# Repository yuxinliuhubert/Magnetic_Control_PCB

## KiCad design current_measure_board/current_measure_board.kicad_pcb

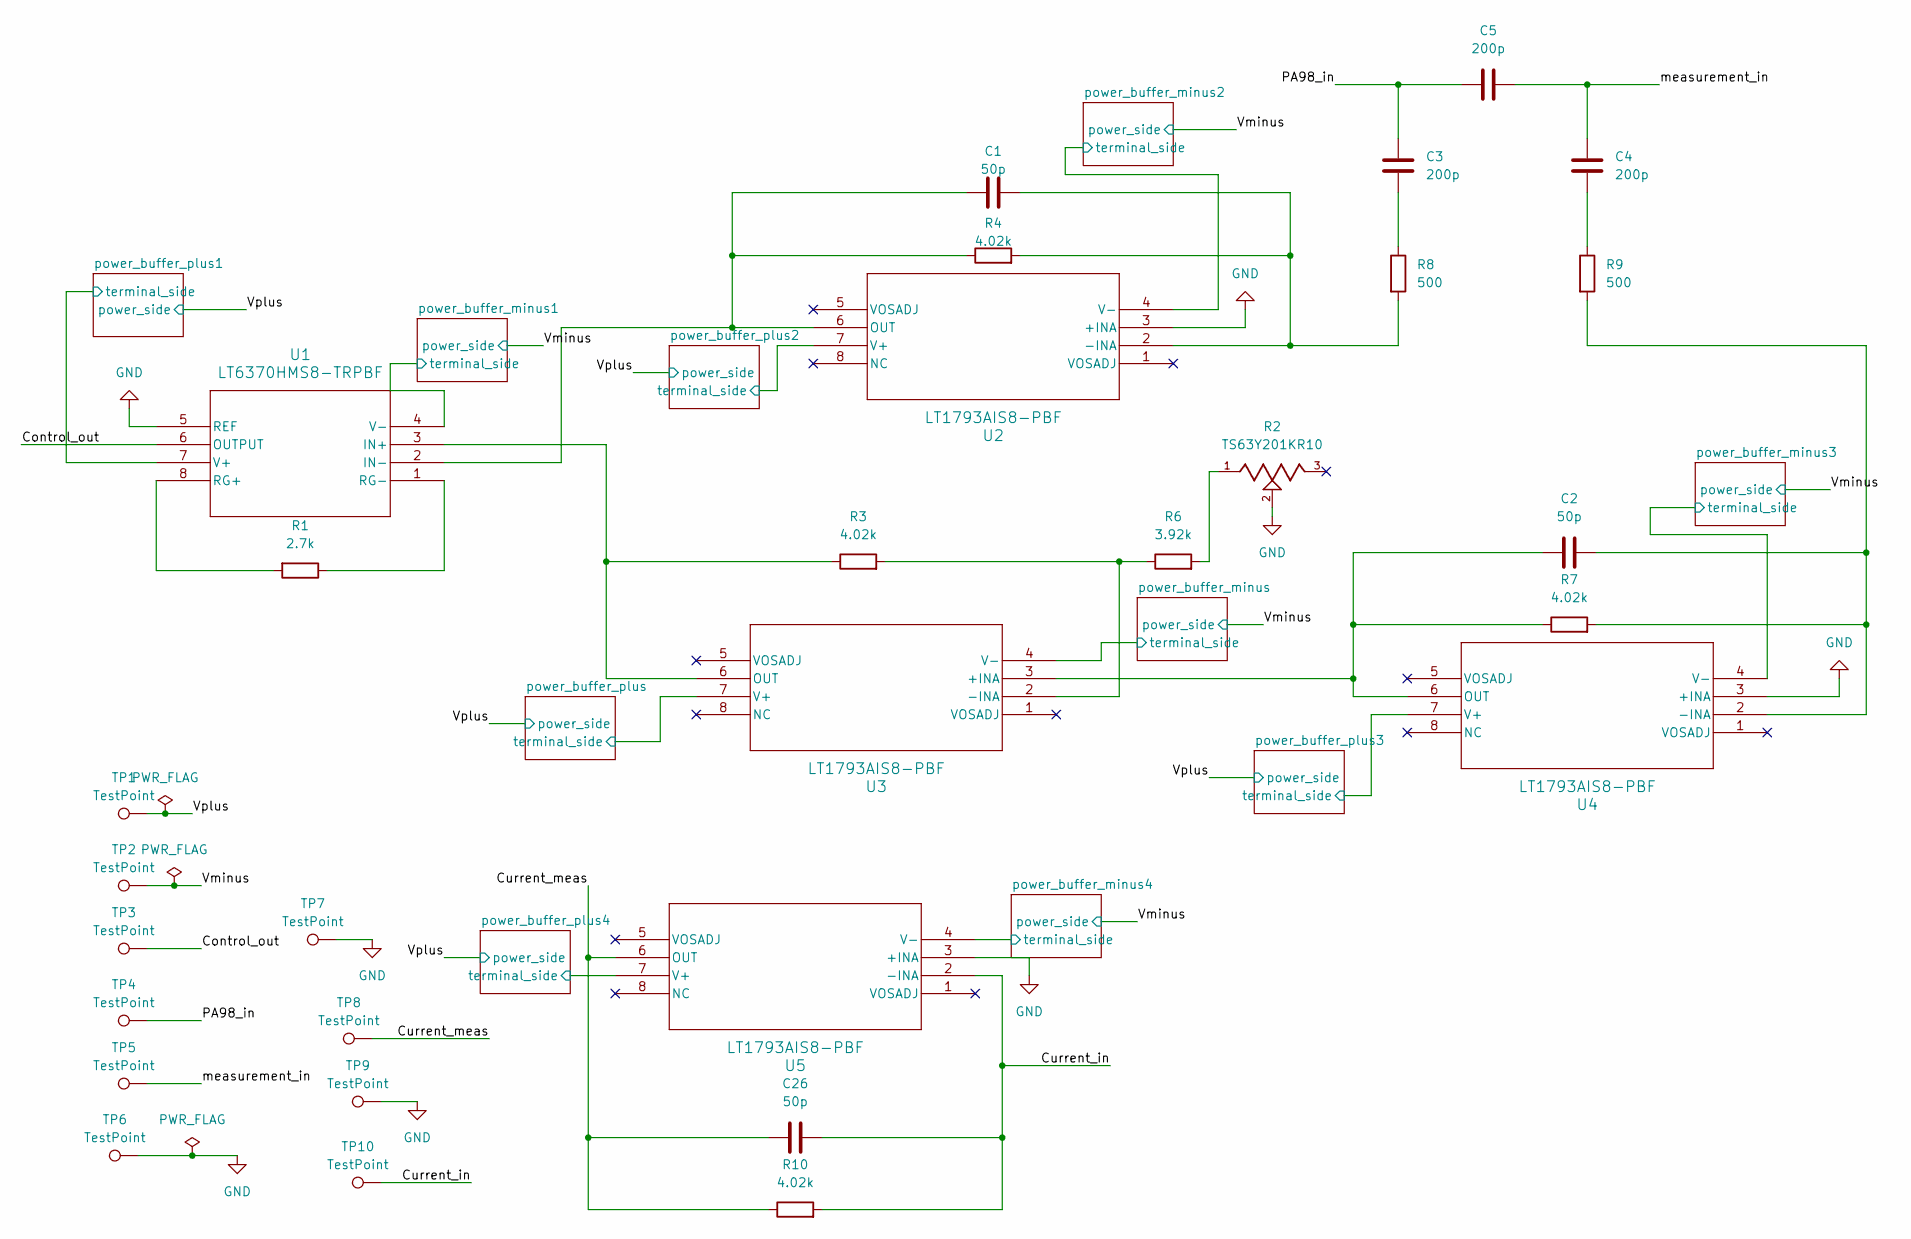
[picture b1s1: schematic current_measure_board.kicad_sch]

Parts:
C1, C2, C26: 50p; CAPC2012X140N(50pF 1206 1 C0G 100V)
C3, C4, C5: 200p; CAPC2012X145N(200pF 0805 0.1err)
R1: 2.7k; RES_TNPW0603_VIS-L(2.7k Ohm 0603 0.1err)
R2: TS63Y201KR10; TRIM_TS63Y201KR10; PARTREV 17-Oct-2018
R3, R4, R7, R10: 4.02k; RESC2012X55N(4.02k Ohm 0805 0.1err)
R6: 3.92k; RES_TNPW0805_VIS-L(3.92k Ohm 0805 0.1)
R8, R9: 500; RESC2012X55N(500 Ohm 0805 0.05err)
TP1, TP2, TP3, TP6, TP7, TP8, TP9: TestPoint; PAD_EXT_2.54x5.08mm
TP4, TP5, TP10: TestPoint; PAD_EXT_0.635x2.54mm
U1: LT6370HMS8-TRPBF; LT6370HMS8_TRPBF_L
U2, U3, U4, U5: LT1793AIS8-PBF; LT1793AIS_8_PBF

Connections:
/Control_out: TP3.1, U1.6 (OUTPUT)
/Current_in: C26.2, R10.2, TP10.1, U5.2 (-INA)
/Current_meas: C26.1, R10.1, TP8.1, U5.6 (OUT)
/PA98_in: C3.2, C5.1, TP4.1
/Vminus: TP2.1, U1.4 (V-), U2.4 (V-), U3.4 (V-), U4.4 (V-), U5.4 (V-); also elsewhere on the board
/Vplus: TP1.1, U1.7 (V+), U2.7 (V+), U3.7 (V+), U4.7 (V+), U5.7 (V+); also elsewhere on the board
/measurement_in: C4.2, C5.2, TP5.1
GND: R2.2, TP6.1, TP7.1, TP9.1, U1.5 (REF), U2.3 (+INA), U4.3 (+INA), U5.3 (+INA); also elsewhere on the board
unnamed: C3.1, R8.1
unnamed: C4.1, R9.1
unnamed: R2.1, R6.2
unnamed: R3.1, U1.3 (IN+), U3.6 (OUT)
unnamed: C1.1, R4.1, U1.2 (IN-), U2.6 (OUT)
unnamed: R1.2, U1.8 (RG+)
unnamed: R1.1, U1.1 (RG-)
unnamed: C1.2, R4.2, R8.2, U2.2 (-INA)
unnamed: C2.1, R7.1, U3.3 (+INA), U4.6 (OUT)
unnamed: R3.2, R6.1, U3.2 (-INA)
unnamed: C2.2, R7.2, R9.2, U4.2 (-INA)

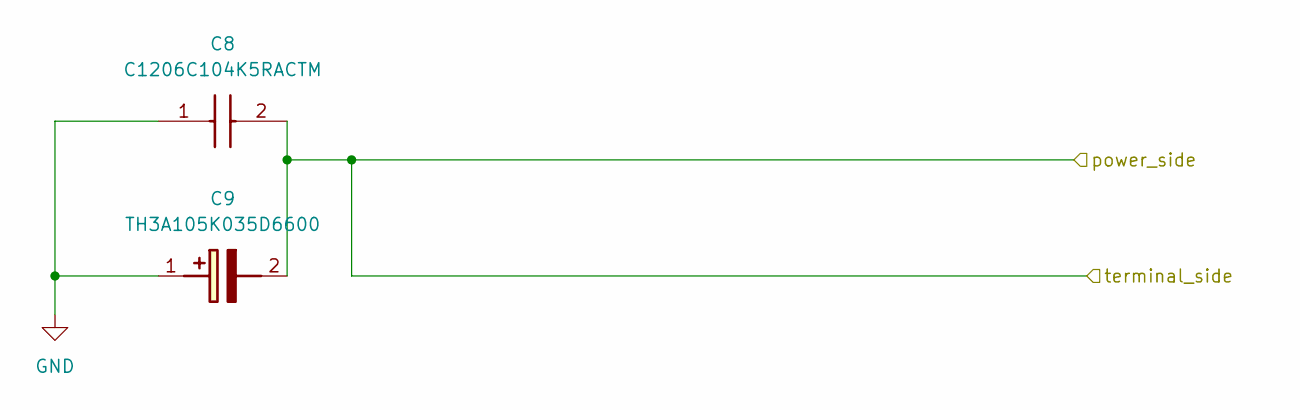
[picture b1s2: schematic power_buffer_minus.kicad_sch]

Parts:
C8: C1206C104K5RACTM; CAPPM3216X180N(0.1uF 1206 0.1acc); Mouser Part Number 80-C1206C104K5RACTM
C9: TH3A105K035D6600; CAPPM3216X180N(1uF 35V 1206 0.1err; Manufacturer_Part_Number TH3A105K035D6600

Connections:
/Vminus: C8.2, C9.2 (-); also elsewhere on the board
GND: C8.1, C9.1 (+); also elsewhere on the board

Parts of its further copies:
C10, C16, C20, C24: C1206C104K5RACTM; CAPPM3216X180N(0.1uF 1206 0.1acc); Mouser Part Number 80-C1206C104K5RACTM
C11, C17, C21, C25: TH3A105K035D6600; CAPPM3216X180N(1uF 35V 1206 0.1err; Manufacturer_Part_Number TH3A105K035D6600

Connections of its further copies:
/Vminus: C10.2, C11.2 (-), C16.2, C17.2 (-), C20.2, C21.2 (-), C24.2, C25.2 (-); also elsewhere on the board
GND: C10.1, C11.1 (+), C16.1, C17.1 (+), C20.1, C21.1 (+), C24.1, C25.1 (+); also elsewhere on the board

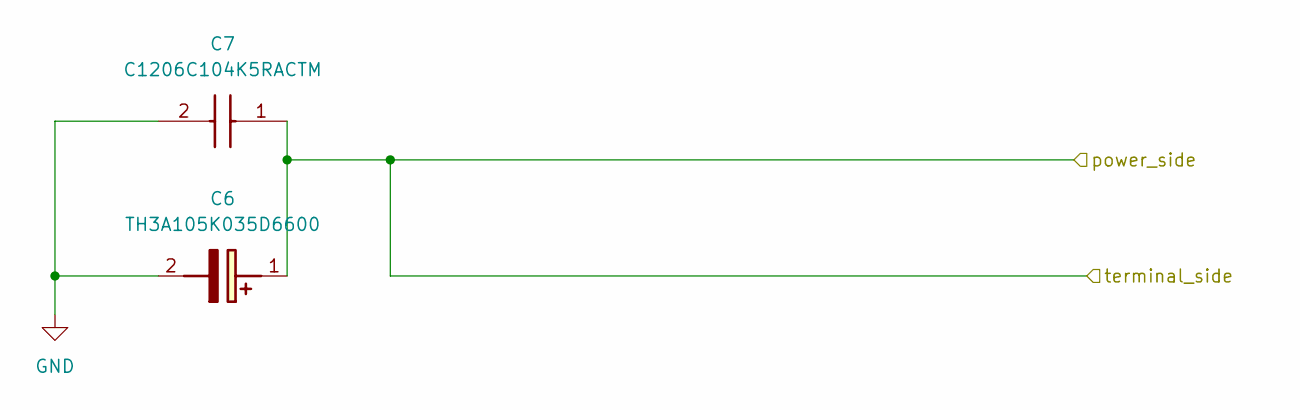
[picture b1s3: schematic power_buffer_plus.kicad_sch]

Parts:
C6: TH3A105K035D6600; CAPPM3216X180N(1uF 35V 1206 0.1err; Manufacturer_Part_Number TH3A105K035D6600
C7: C1206C104K5RACTM; CAPPM3216X180N(0.1uF 1206 0.1acc); Mouser Part Number 80-C1206C104K5RACTM

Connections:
/Vplus: C6.1 (+), C7.1; also elsewhere on the board
GND: C6.2 (-), C7.2; also elsewhere on the board

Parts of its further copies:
C12, C14, C18, C22: C1206C104K5RACTM; CAPPM3216X180N(0.1uF 1206 0.1acc); Mouser Part Number 80-C1206C104K5RACTM
C13, C15, C19, C23: TH3A105K035D6600; CAPPM3216X180N(1uF 35V 1206 0.1err; Manufacturer_Part_Number TH3A105K035D6600

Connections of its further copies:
/Vplus: C12.1, C13.1 (+), C14.1, C15.1 (+), C18.1, C19.1 (+), C22.1, C23.1 (+); also elsewhere on the board
GND: C12.2, C13.2 (-), C14.2, C15.2 (-), C18.2, C19.2 (-), C22.2, C23.2 (-); also elsewhere on the board

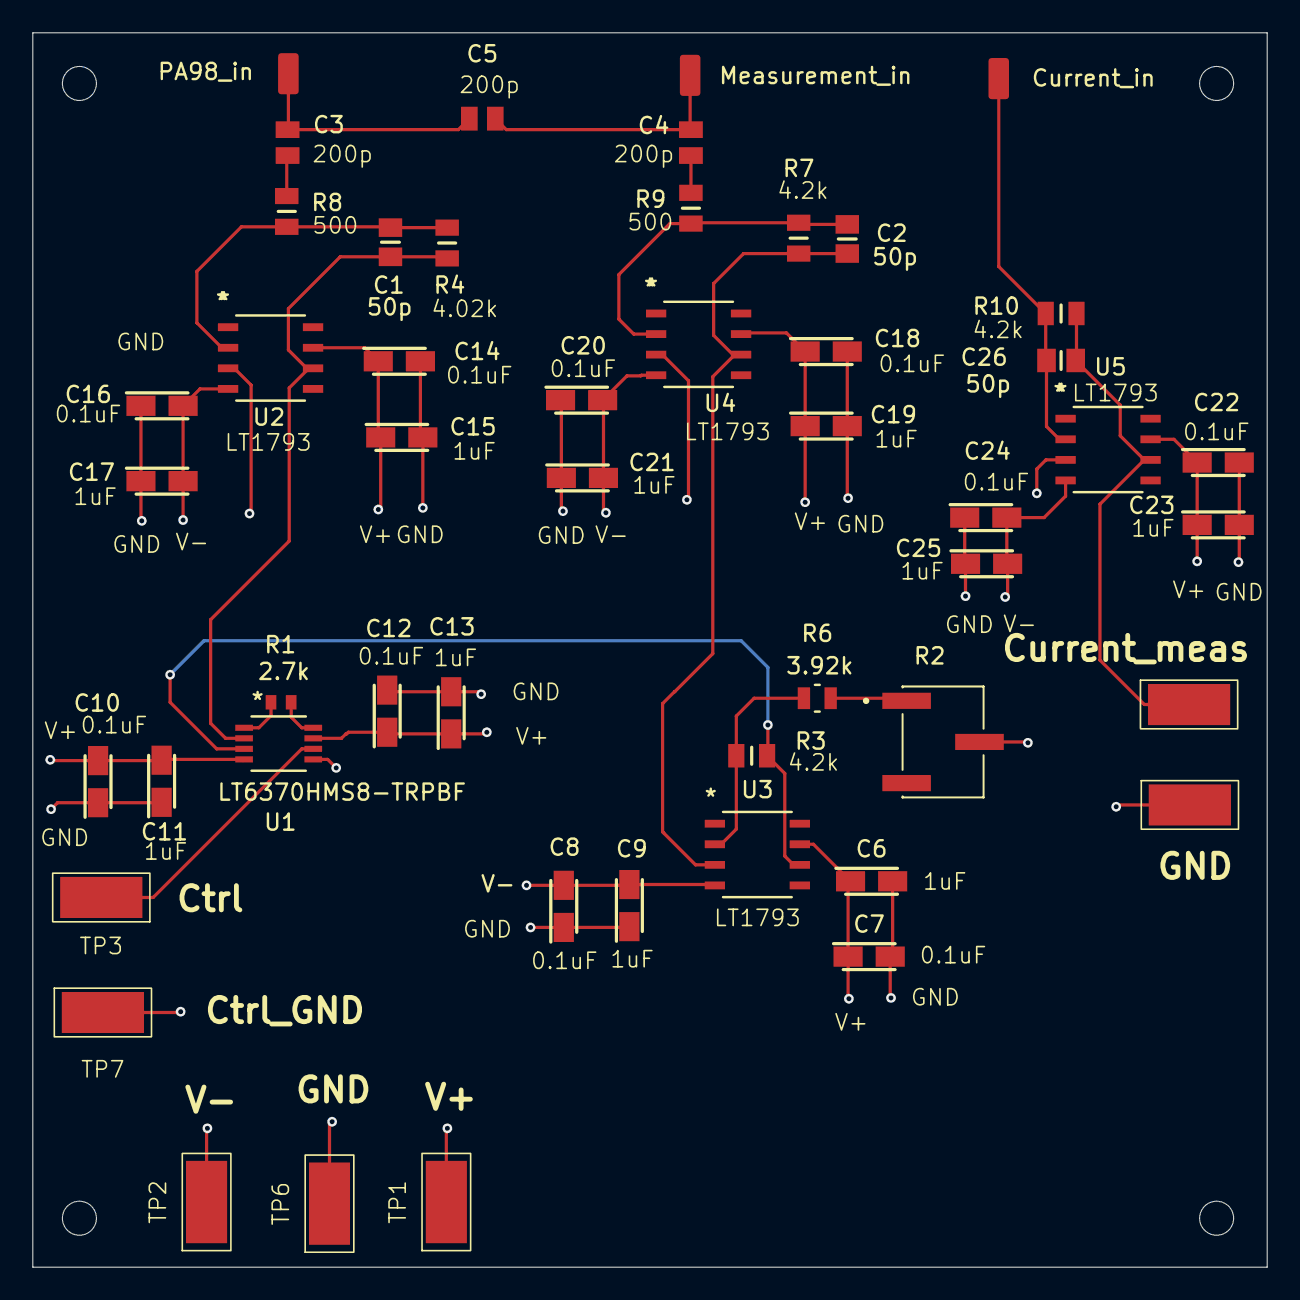
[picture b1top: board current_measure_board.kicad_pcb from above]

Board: 6 copper layers, 76.2 x 76.2 mm, 50 parts (0 on the bottom side), 19 nets.

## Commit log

2025-04-14 Fixed LTSpice simulation values
2025-05-07 old 250H checkpoint 1 code preserved here
2025-05-08 high impedance section draft done
2025-05-09 Power buffer done
2026-01-20 current board update
